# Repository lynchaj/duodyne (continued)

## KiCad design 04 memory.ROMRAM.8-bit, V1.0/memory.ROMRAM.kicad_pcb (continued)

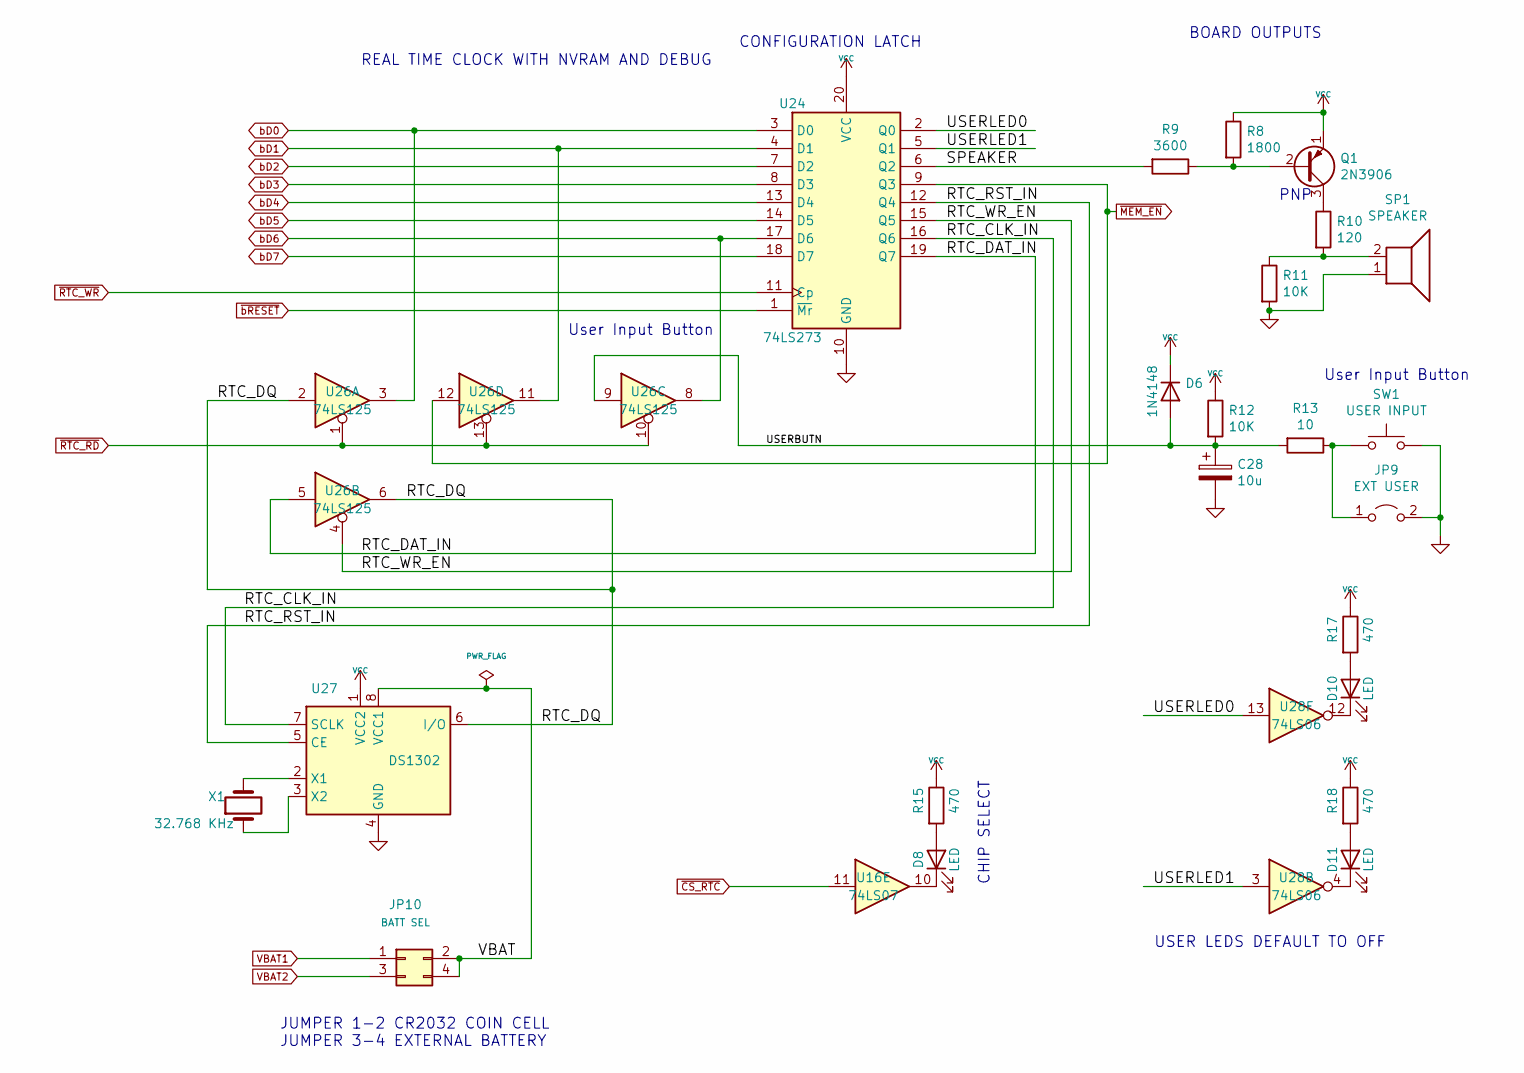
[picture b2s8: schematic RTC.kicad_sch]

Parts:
C28: 10u; CP_Radial_D5.0mm_P2.50mm
D6: 1N4148; D_DO-35_SOD27_P7.62mm_Horizontal
D8, D10, D11: LED; LED_D3.0mm_Horizontal_O3.81mm_Z2.0mm
JP9: EXT USER; PinHeader_1x02_P2.54mm_Horizontal
JP10: BATT SEL; PinHeader_2x02_P2.54mm_Vertical
Q1: 2N3906; TO-92_Inline
R8: 1800; R_Axial_DIN0207_L6.3mm_D2.5mm_P7.62mm_Horizontal
R9: 3600; R_Axial_DIN0207_L6.3mm_D2.5mm_P7.62mm_Horizontal
R10: 120; R_Axial_DIN0207_L6.3mm_D2.5mm_P7.62mm_Horizontal
R11, R12: 10K; R_Axial_DIN0207_L6.3mm_D2.5mm_P7.62mm_Horizontal
R13: 10; R_Axial_DIN0207_L6.3mm_D2.5mm_P7.62mm_Horizontal
R15, R17, R18: 470; R_Axial_DIN0207_L6.3mm_D2.5mm_P7.62mm_Horizontal
SP1: SPEAKER; MagneticBuzzer_StarMicronics_HMB-06_HMB-12
SW1: USER INPUT; SW_Tactile_SPST_Angled_PTS645Vx58-2LFS
U16: 74LS07; DIP-14_W7.62mm
U24: 74LS273; DIP-20_W7.62mm
U26: 74LS125; DIP-14_W7.62mm
U27: DS1302; DIP-8_W7.62mm
U28: 74LS06; DIP-14_W7.62mm
X1: 32.768 KHz; Crystal_AT310_D3.0mm_L10.0mm_Horizontal

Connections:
/RTC/RTC_CLK_IN: U24.16 (Q6), U27.7 (SCLK)
/RTC/RTC_DAT_IN: U24.19 (Q7), U26.5
/RTC/RTC_DQ: U26.2, U26.6, U27.6 (I/O)
/RTC/RTC_RST_IN: U24.12 (Q4), U27.5 (CE)
/RTC/RTC_WR_EN: U24.15 (Q5), U26.4
/RTC/SPEAKER: R9.2, U24.6 (Q2)
/RTC/USERBUTN: C28.1, D6.2 (A), R12.2, R13.2, U26.9
/RTC/USERLED0: U24.2 (Q0), U28.13
/RTC/USERLED1: U24.5 (Q1), U28.3
/RTC/VBAT: JP10.2, JP10.4, U27.8 (VCC1)
GND: C28.2, JP9.2 (B), R11.2, SP1.1, SW1.2, U24.10 (GND), U27.4 (GND); also elsewhere on the board
unnamed: D8.1 (K), U16.10
unnamed: D8.2 (A), R15.2
unnamed: D10.1 (K), U28.12
unnamed: D10.2 (A), R17.2
unnamed: D11.1 (K), U28.4
unnamed: D11.2 (A), R18.2
unnamed: JP9.1 (A), R13.1, SW1.1
unnamed: Q1.2 (B), R8.2, R9.1
unnamed: Q1.3 (C), R10.1
unnamed: R10.2, R11.1, SP1.2
unnamed: U27.2 (X1), X1.2
unnamed: U27.3 (X2), X1.1
VBAT1: JP10.1; also elsewhere on the board
VBAT2: JP10.3; also elsewhere on the board
VCC: D6.1 (K), Q1.1 (E), R8.1, R12.1, R15.1, R17.1, R18.1, U24.20 (VCC), U27.1 (VCC2); also elsewhere on the board
bD0: U24.3 (D0), U26.3; also elsewhere on the board
bD1: U24.4 (D1), U26.11; also elsewhere on the board
bD2: U24.7 (D2); also elsewhere on the board
bD3: U24.8 (D3); also elsewhere on the board
bD4: U24.13 (D4); also elsewhere on the board
bD5: U24.14 (D5); also elsewhere on the board
bD6: U24.17 (D6), U26.8; also elsewhere on the board
bD7: U24.18 (D7); also elsewhere on the board
~CS_RTC: U16.11; also elsewhere on the board
~MEM_EN: U24.9 (Q3), U26.12; also elsewhere on the board
~RTC_RD: U26.1, U26.10, U26.13; also elsewhere on the board
~RTC_WR: U24.11 (Cp); also elsewhere on the board
~bRESET: U24.1 (~Mr); also elsewhere on the board

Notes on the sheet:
PNP
User Input Button
BOARD OUTPUTS
CONFIGURATION LATCH
JUMPER 1-2 CR2032 COIN CELL JUMPER 3-4 EXTERNAL BATTERY
CHIP SELECT
USER LEDS DEFAULT TO OFF
REAL TIME CLOCK WITH NVRAM AND DEBUG

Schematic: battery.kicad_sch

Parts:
BT1: Battery; BatteryHolder_Keystone_103_1x20mm
JP1, JP4, JP5, JP6, JP8, JP11, JP12, JP13: BYPASS; PinHeader_1x02_P2.54mm_Vertical
JP2: BATT SEL; PinHeader_2x02_P2.54mm_Vertical
K1: VCC TOL 0; PinHeader_1x03_P2.54mm_Vertical
K2: VCC TOL 2; PinHeader_1x03_P2.54mm_Vertical
K3: VCC TOL 3; PinHeader_1x03_P2.54mm_Vertical
K5: VCC TOL 1; PinHeader_1x03_P2.54mm_Vertical
U5, U13, U18, U19: DS1210; DIP-8_W7.62mm

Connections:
/battery/V2032: BT1.1 (+), JP2.1
GND: BT1.2 (-), JP2.3, K1.3, K2.3, K3.3, K5.3, U5.4 (GND), U13.4 (GND), U18.4 (GND), U19.4 (GND); also elsewhere on the board
unnamed: K1.2, U5.3 (TOL)
unnamed: K2.2, U18.3 (TOL)
unnamed: K3.2, U19.3 (TOL)
unnamed: K5.2, U13.3 (TOL)
VBAT1: JP2.2, U5.2 (VBAT1), U13.2 (VBAT1), U18.2 (VBAT1), U19.2 (VBAT1); also elsewhere on the board
VBAT2: JP2.4, U5.7 (VBAT2), U13.7 (VBAT2), U18.7 (VBAT2), U19.7 (VBAT2); also elsewhere on the board
VCC: JP1.1 (A), JP5.1 (A), JP8.1 (A), JP12.1 (A), U5.8 (VCCI), U13.8 (VCCI), U18.8 (VCCI), U19.8 (VCCI); also elsewhere on the board
VCC_SRAM0: JP1.2 (B), K1.1, U5.1 (VCCO); also elsewhere on the board
VCC_SRAM1: JP5.2 (B), K5.1, U13.1 (VCCO); also elsewhere on the board
VCC_SRAM2: JP8.2 (B), K2.1, U18.1 (VCCO); also elsewhere on the board
VCC_SRAM3: JP12.2 (B), K3.1, U19.1 (VCCO); also elsewhere on the board
~CEO0: JP4.2 (B), U5.6 (~CEO); also elsewhere on the board
~CEO1: JP6.2 (B), U13.6 (~CEO); also elsewhere on the board
~CEO2: JP11.2 (B), U18.6 (~CEO); also elsewhere on the board
~CEO3: JP13.2 (B), U19.6 (~CEO); also elsewhere on the board
~CS_RAM0: JP4.1 (A), U5.5 (~CE); also elsewhere on the board
~CS_RAM1: JP6.1 (A), U13.5 (~CE); also elsewhere on the board
~CS_RAM2: JP11.1 (A), U18.5 (~CE); also elsewhere on the board
~CS_RAM3: JP13.1 (A), U19.5 (~CE); also elsewhere on the board

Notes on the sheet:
NOTE: K1 VCC TOLERANCE 1-2 CLOSED 10% 2-3 CLOSED 5%
JP1 AND JP3 U2 DS1210 INSTALLED CLOSE BOTH TO BYPASS DEFAULT BOTH OPEN
NOTE: K5 VCC TOLERANCE 1-2 CLOSED 10% 2-3 CLOSED 5%
JUMPER 1-2 CR2032 COIN CELL JUMPER 3-4 EXTERNAL BATTERY
JP4 AND JP5 U11 DS1210 INSTALLED CLOSE BOTH TO BYPASS DEFAULT BOTH OPEN

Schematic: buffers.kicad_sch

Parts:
U6, U7, U8, U17: 74LS244; DIP-20_W7.62mm
U14: 74LS245; DIP-20_W7.62mm

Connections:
A0: U6.2 (I0a); also elsewhere on the board
A1: U6.4 (I1a); also elsewhere on the board
A2: U6.6 (I2a); also elsewhere on the board
A3: U6.8 (I3a); also elsewhere on the board
A4: U6.11 (I0b); also elsewhere on the board
A5: U6.13 (I1b); also elsewhere on the board
A6: U6.15 (I2b); also elsewhere on the board
A7: U6.17 (I3b); also elsewhere on the board
A8: U7.2 (I0a); also elsewhere on the board
A9: U7.4 (I1a); also elsewhere on the board
A10: U7.6 (I2a); also elsewhere on the board
A11: U7.8 (I3a); also elsewhere on the board
A12: U7.11 (I0b); also elsewhere on the board
A13: U7.13 (I1b); also elsewhere on the board
A14: U7.15 (I2b); also elsewhere on the board
A15: U7.17 (I3b); also elsewhere on the board
A16: U8.2 (I0a); also elsewhere on the board
A17: U8.4 (I1a); also elsewhere on the board
A18: U8.6 (I2a); also elsewhere on the board
A19: U8.8 (I3a); also elsewhere on the board
A20: U8.11 (I0b); also elsewhere on the board
A21: U8.13 (I1b); also elsewhere on the board
D0: U14.2 (A0); also elsewhere on the board
D1: U14.3 (A1); also elsewhere on the board
D2: U14.4 (A2); also elsewhere on the board
D3: U14.5 (A3); also elsewhere on the board
D4: U14.6 (A4); also elsewhere on the board
D5: U14.7 (A5); also elsewhere on the board
D6: U14.8 (A6); also elsewhere on the board
D7: U14.9 (A7); also elsewhere on the board
GND: U6.10 (GND), U7.10 (GND), U8.10 (GND), U14.10 (GND), U17.10 (GND); also elsewhere on the board
unnamed 146: U17.2 (I0a); also elsewhere on the board
VCC: U6.20 (VCC), U7.20 (VCC), U8.20 (VCC), U14.20 (VCC), U17.20 (VCC); also elsewhere on the board
ZERO: U6.1 (OEa), U6.19 (OEb), U7.1 (OEa), U7.19 (OEb), U8.1 (OEa), U8.19 (OEb), U17.1 (OEa), U17.19 (OEb); also elsewhere on the board
bA0: U6.18 (O0a); also elsewhere on the board
bA1: U6.16 (O1a); also elsewhere on the board
bA2: U6.14 (O2a); also elsewhere on the board
bA3: U6.12 (O3a); also elsewhere on the board
bA4: U6.9 (O0b); also elsewhere on the board
bA5: U6.7 (O1b); also elsewhere on the board
bA6: U6.5 (O2b); also elsewhere on the board
bA7: U6.3 (O3b); also elsewhere on the board
bA8: U7.18 (O0a); also elsewhere on the board
bA9: U7.16 (O1a); also elsewhere on the board
bA10: U7.14 (O2a); also elsewhere on the board
bA11: U7.12 (O3a); also elsewhere on the board
bA12: U7.9 (O0b); also elsewhere on the board
bA13: U7.7 (O1b); also elsewhere on the board
bA14: U7.5 (O2b); also elsewhere on the board
bA15: U7.3 (O3b); also elsewhere on the board
bA16: U8.18 (O0a); also elsewhere on the board
bA17: U8.16 (O1a); also elsewhere on the board
bA18: U8.14 (O2a); also elsewhere on the board
bA19: U8.12 (O3a); also elsewhere on the board
bA20: U8.9 (O0b); also elsewhere on the board
bA21: U8.7 (O1b); also elsewhere on the board
bD0: U14.18 (B0); also elsewhere on the board
bD1: U14.17 (B1); also elsewhere on the board
bD2: U14.16 (B2); also elsewhere on the board
bD3: U14.15 (B3); also elsewhere on the board
bD4: U14.14 (B4); also elsewhere on the board
bD5: U14.13 (B5); also elsewhere on the board
bD6: U14.12 (B6); also elsewhere on the board
bD7: U14.11 (B7); also elsewhere on the board
~BUS_EN: U14.19 (CE); also elsewhere on the board
~IORQ: U17.11 (I0b); also elsewhere on the board
~M1: U17.8 (I3a); also elsewhere on the board
~MREQ: U17.13 (I1b); also elsewhere on the board
~RD: U14.1 (A->B), U17.17 (I3b); also elsewhere on the board
~WR: U17.15 (I2b); also elsewhere on the board
~bIORQ: U17.9 (O0b); also elsewhere on the board
~bM1: U17.12 (O3a); also elsewhere on the board
~bMREQ: U17.7 (O1b); also elsewhere on the board
~bRD: U17.3 (O3b); also elsewhere on the board
~bRESET: U17.18 (O0a); also elsewhere on the board
~bWR: U17.5 (O2b); also elsewhere on the board

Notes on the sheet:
Z80 BUS INTERFACE
Note: Buffers and Transceivers respond to both IO and MEM cycles

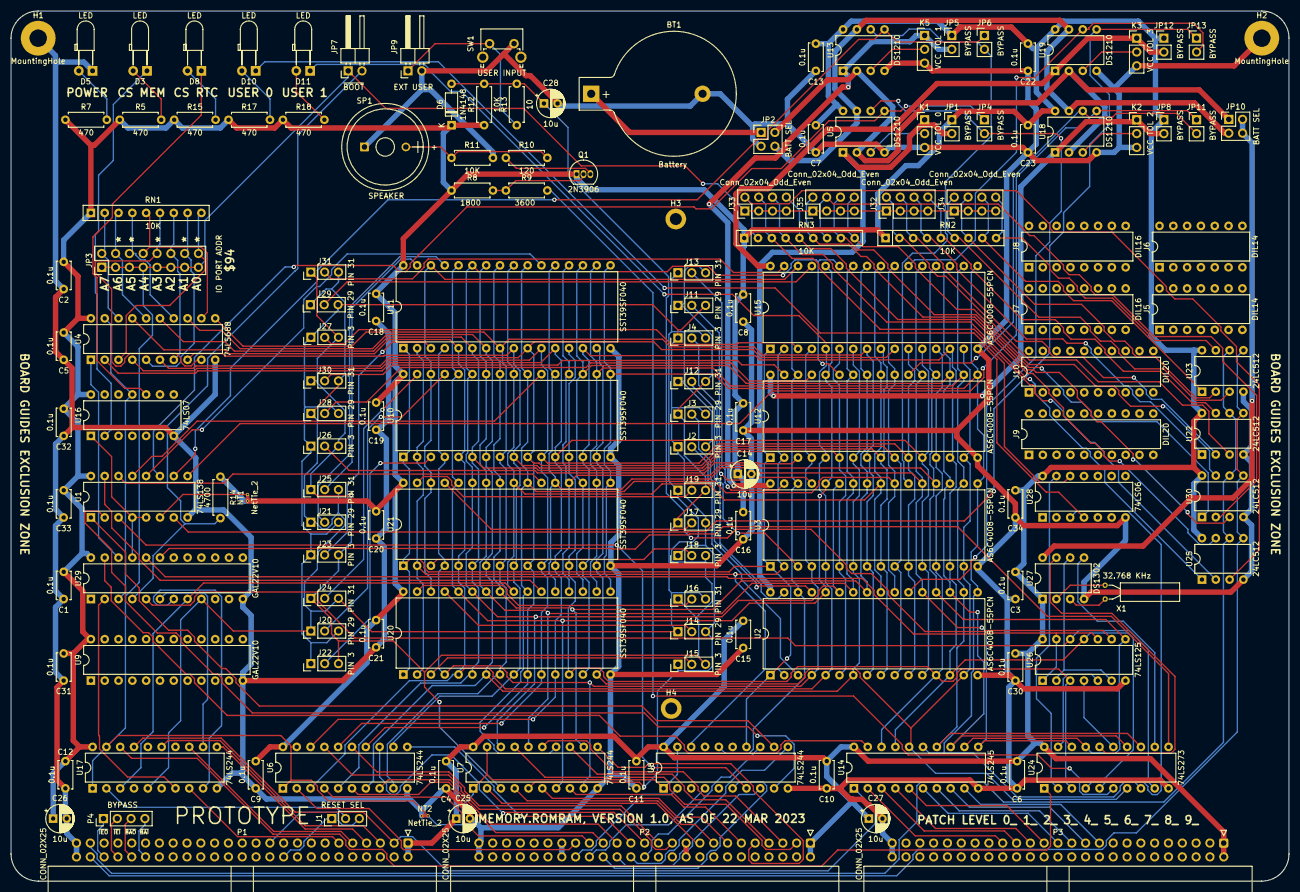
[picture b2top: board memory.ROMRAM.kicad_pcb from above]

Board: 2 copper layers, 235.0 x 160.0 mm, 150 parts (0 on the bottom side), 190 nets.

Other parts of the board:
J1: RESET SEL; PinHeader_1x03_P2.54mm_Vertical
J32, J33, J34, J35: Conn_02x04_Odd_Even; PinHeader_2x04_P2.54mm_Vertical
NT1, NT2: NetTie_2; NetTie-2_THT_Pad0.3mm
RN2, RN3: 10K; R_Array_SIP9
U22, U23, U25, U30: 24LC512; DIP-8_W7.62mm

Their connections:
GND: NT2.1, U22.4 (GND), U23.4 (GND), U25.4 (GND), U30.4 (GND); also elsewhere on the board
I2C_SCL: U22.6 (SCL), U23.6 (SCL), U25.6 (SCL), U30.6 (SCL); also elsewhere on the board
I2C_SDA: U22.5 (SDA), U23.5 (SDA), U25.5 (SDA), U30.5 (SDA); also elsewhere on the board
unnamed 146: J1.2; also elsewhere on the board
unnamed: J32.2, RN2.2 (R1), U22.3 (A2)
unnamed: J32.4, RN2.3 (R2), U22.2 (A1)
unnamed: J32.6, RN2.4 (R3), U22.1 (A0)
unnamed: J32.8, RN2.5 (R4), U22.7 (WP)
unnamed: J33.2, RN3.2 (R1), U25.3 (A2)
unnamed: J33.4, RN3.3 (R2), U25.2 (A1)
unnamed: J33.6, RN3.4 (R3), U25.1 (A0)
unnamed: J33.8, RN3.5 (R4), U25.7 (WP)
unnamed: J34.2, RN2.6 (R5), U23.3 (A2)
unnamed: J34.4, RN2.7 (R6), U23.2 (A1)
unnamed: J34.6, RN2.8 (R7), U23.1 (A0)
unnamed: J34.8, RN2.9 (R8), U23.7 (WP)
unnamed: J35.2, RN3.6 (R5), U30.3 (A2)
unnamed: J35.4, RN3.7 (R6), U30.2 (A1)
unnamed: J35.6, RN3.8 (R7), U30.1 (A0)
unnamed: J35.8, RN3.9 (R8), U30.7 (WP)
ONE: NT1.2; also elsewhere on the board
VCC: NT1.1, RN2.1 (common), RN3.1 (common), U22.8 (VCC), U23.8 (VCC), U25.8 (VCC), U30.8 (VCC); also elsewhere on the board
ZERO: J32.1, J32.3, J32.5, J32.7, J33.1, J33.3, J33.5, J33.7, J34.1, J34.3, J34.5, J34.7, J35.1, J35.3, J35.5, J35.7, NT2.2; also elsewhere on the board
~RES_IN: J1.1; also elsewhere on the board
~RES_OUT: J1.3; also elsewhere on the board

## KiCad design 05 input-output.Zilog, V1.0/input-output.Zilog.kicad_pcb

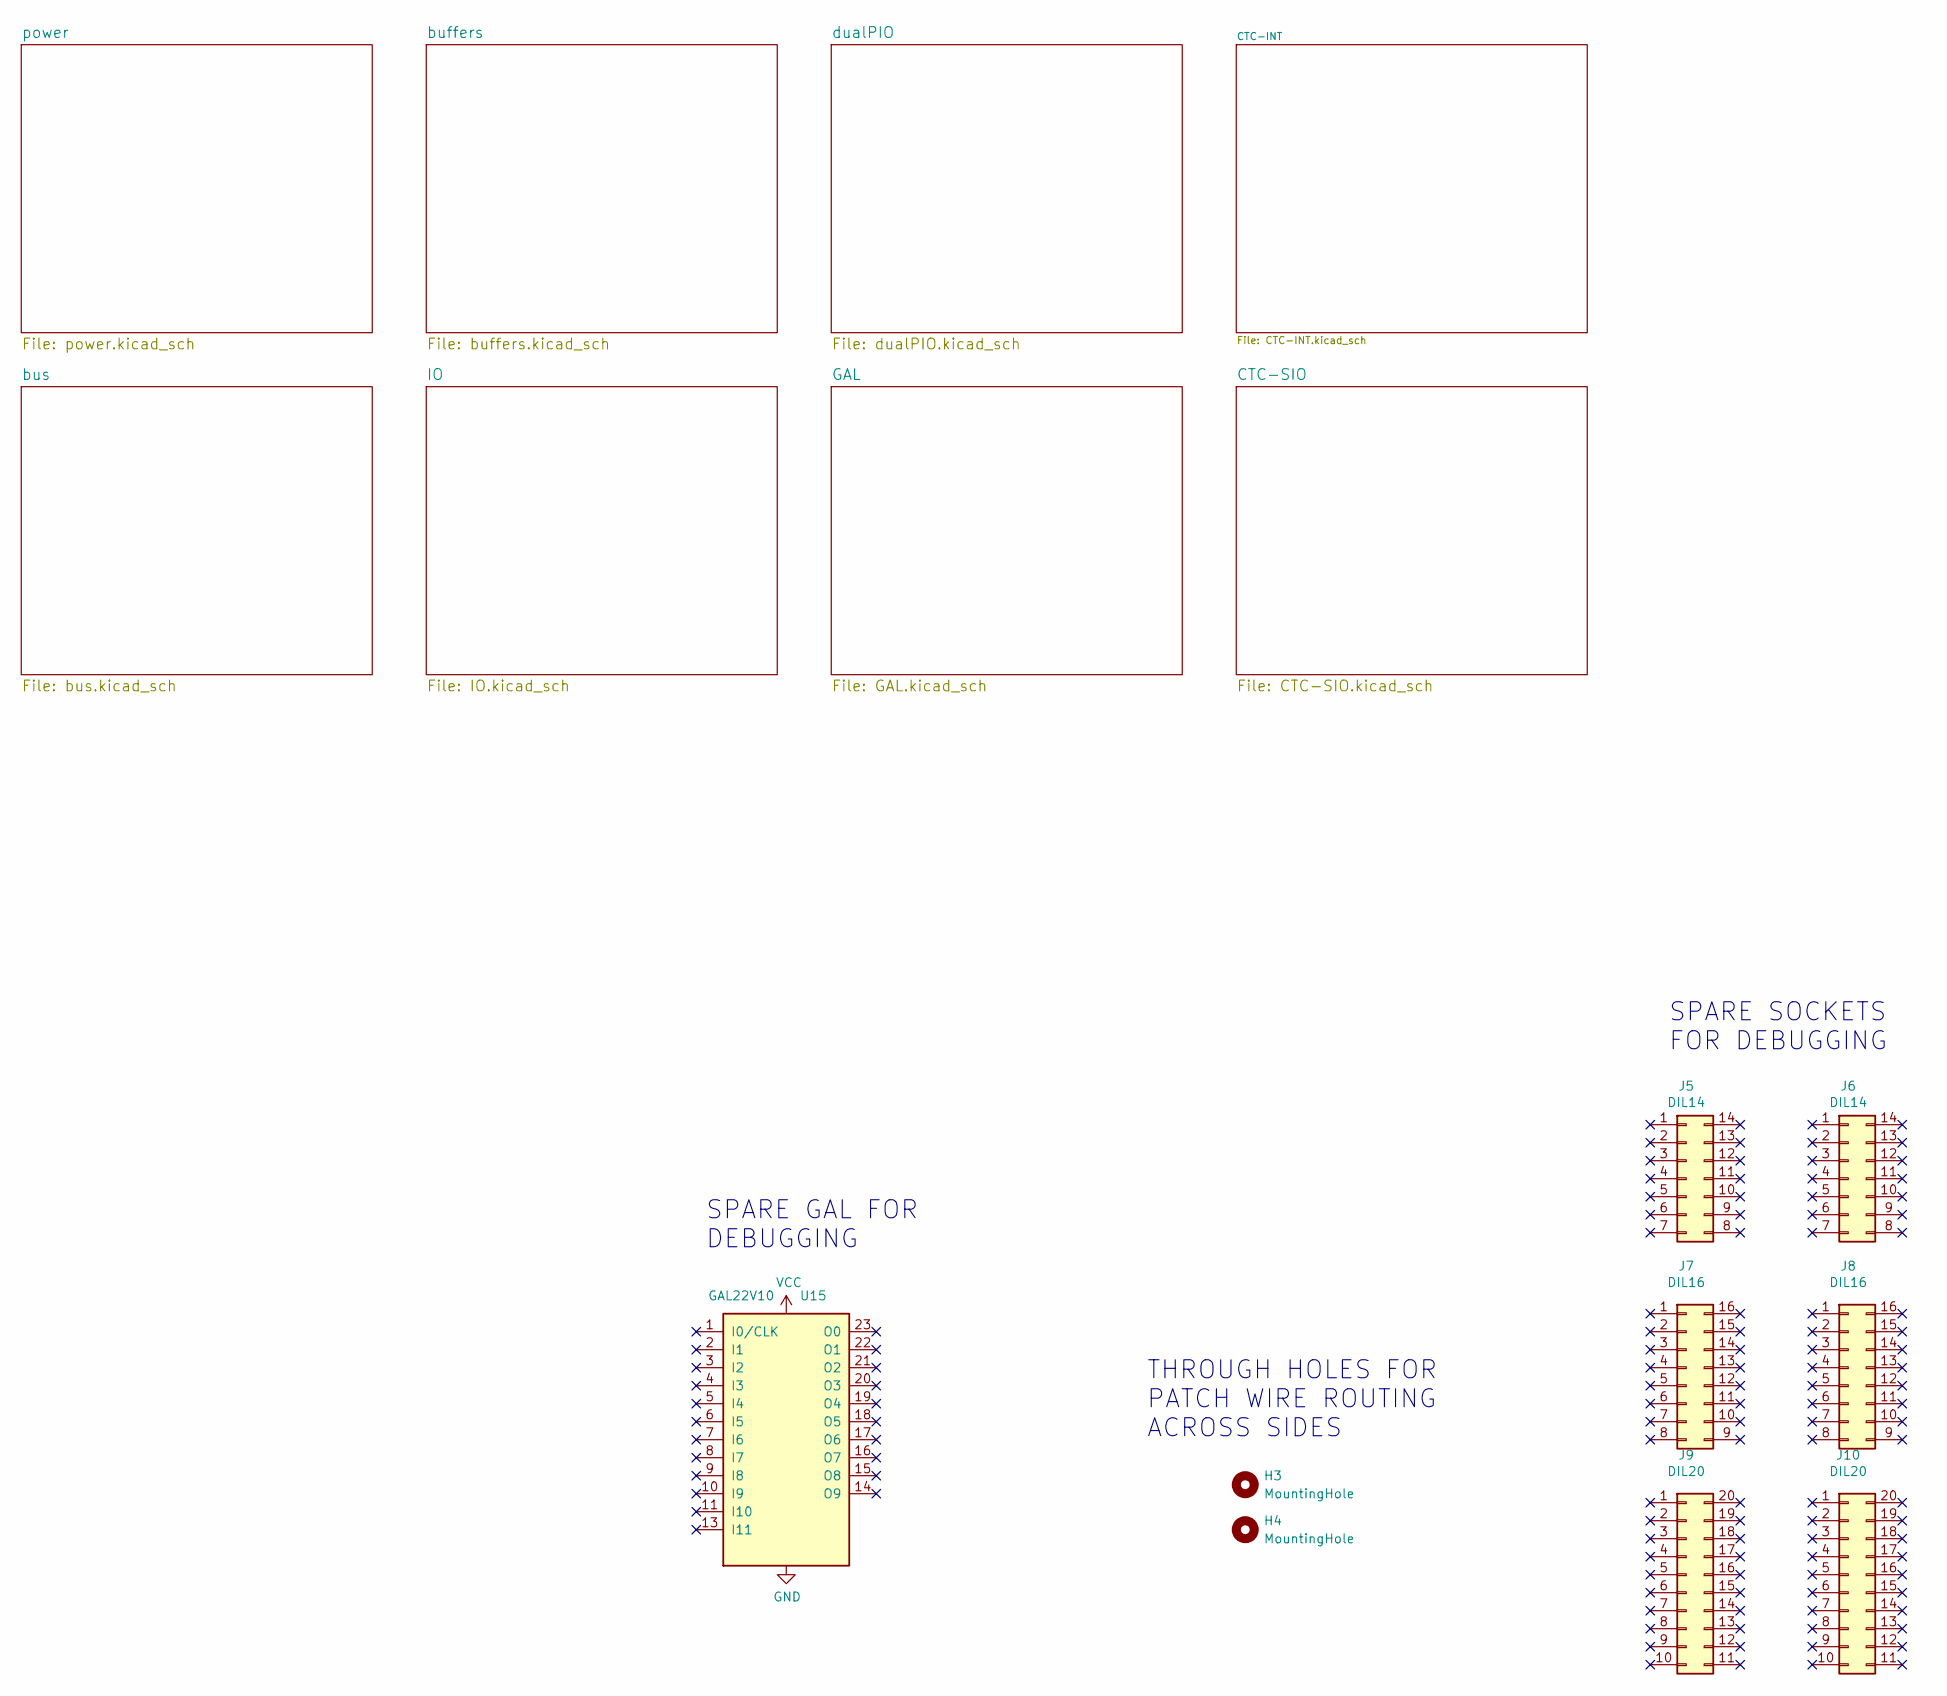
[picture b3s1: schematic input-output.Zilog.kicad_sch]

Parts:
H3, H4: MountingHole; MountingHole_2.2mm_M2_DIN965_Pad
J5, J6: DIL14; DIP-14_W7.62mm
J7, J8: DIL16; DIP-16_W7.62mm
J9, J10: DIL20; DIP-20_W7.62mm
U15: GAL22V10; DIP-24_W7.62mm

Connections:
GND: U15.12 (GND); also elsewhere on the board
VCC: U15.24 (VCC); also elsewhere on the board

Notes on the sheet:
THROUGH HOLES FOR PATCH WIRE ROUTING ACROSS SIDES
SPARE GAL FOR DEBUGGING
SPARE SOCKETS FOR DEBUGGING

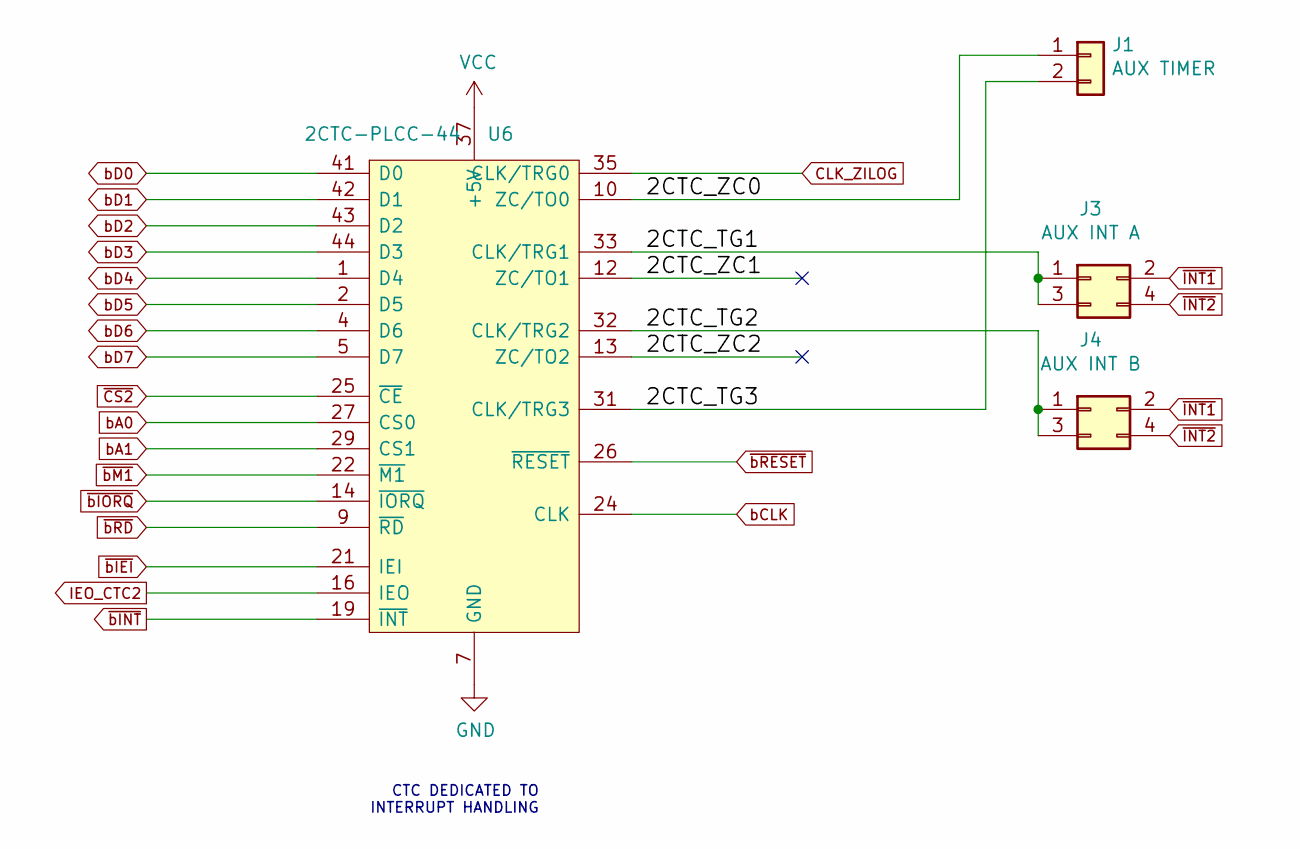
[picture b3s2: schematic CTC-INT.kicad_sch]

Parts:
J1: AUX TIMER; PinHeader_1x02_P2.54mm_Vertical
J3: AUX INT A; PinHeader_2x02_P2.54mm_Vertical
J4: AUX INT B; PinHeader_2x02_P2.54mm_Vertical
U6: 2CTC-PLCC-44; PLCC-44_16.6x16.6mm_P1.27mm; Manufacturer_Part_Number Z84C3010PEG; Mouser Part Number 692-Z84C3010PEG

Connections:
/CTC-INT/2CTC_TG1: J3.1, J3.3, U6.33 (CLK/TRG1)
/CTC-INT/2CTC_TG2: J4.1, J4.3, U6.32 (CLK/TRG2)
/CTC-INT/2CTC_TG3: J1.2, U6.31 (CLK/TRG3)
/CTC-INT/2CTC_ZC0: J1.1, U6.10 (ZC/TO0)
/CTC-INT/2CTC_ZC1: U6.12 (ZC/TO1)
/CTC-INT/2CTC_ZC2: U6.13 (ZC/TO2)
CLK_ZILOG: U6.35 (CLK/TRG0); also elsewhere on the board
GND: U6.7 (GND); also elsewhere on the board
IEO_CTC2: U6.16 (IEO); also elsewhere on the board
VCC: U6.37 (+5V); also elsewhere on the board
bA0: U6.27 (CS0); also elsewhere on the board
bA1: U6.29 (CS1); also elsewhere on the board
bCLK: U6.24 (CLK); also elsewhere on the board
bD0: U6.41 (D0); also elsewhere on the board
bD1: U6.42 (D1); also elsewhere on the board
bD2: U6.43 (D2); also elsewhere on the board
bD3: U6.44 (D3); also elsewhere on the board
bD4: U6.1 (D4); also elsewhere on the board
bD5: U6.2 (D5); also elsewhere on the board
bD6: U6.4 (D6); also elsewhere on the board
bD7: U6.5 (D7); also elsewhere on the board
~CS2: U6.25 (~CE); also elsewhere on the board
~INT1: J3.2, J4.2; also elsewhere on the board
~INT2: J3.4, J4.4; also elsewhere on the board
~bIEI: U6.21 (IEI); also elsewhere on the board
~bINT: U6.19 (~INT); also elsewhere on the board
~bIORQ: U6.14 (~IORQ); also elsewhere on the board
~bM1: U6.22 (~M1); also elsewhere on the board
~bRD: U6.9 (~RD); also elsewhere on the board
~bRESET: U6.26 (~RESET); also elsewhere on the board

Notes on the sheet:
CTC DEDICATED TO INTERRUPT HANDLING

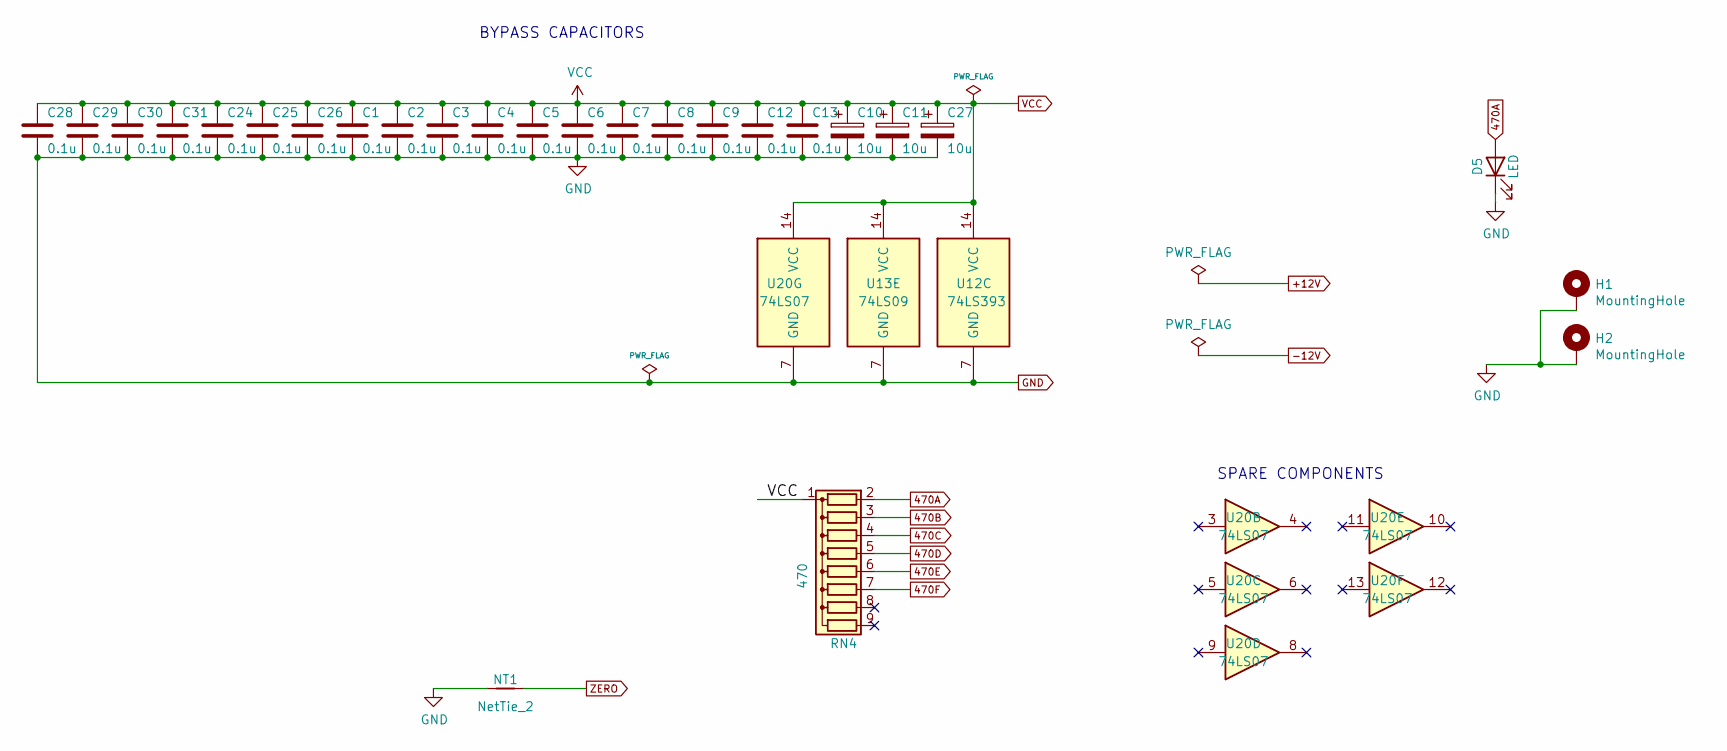
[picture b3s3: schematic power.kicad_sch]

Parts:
C1, C2, C3, C4, C5, C6, C7, C8, C9, C12, C13, C24, C25, C26, C28, C29, C30, C31: 0.1u; C_Disc_D5.0mm_W2.5mm_P5.00mm
C10, C11, C27: 10u; CP_Radial_D5.0mm_P2.50mm
D5: LED; LED_D3.0mm_Horizontal_O3.81mm_Z2.0mm
H1, H2: MountingHole; MountingHole_3.2mm_M3_Pad
NT1: NetTie_2; NetTie-2_THT_Pad0.3mm
RN4: 470; R_Array_SIP9
U12: 74LS393; DIP-14_W7.62mm
U13: 74LS09; DIP-14_W7.62mm
U20: 74LS07; DIP-14_W7.62mm

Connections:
470A: D5.2 (A), RN4.2 (R1)
470B: RN4.3 (R2); also elsewhere on the board
470C: RN4.4 (R3); also elsewhere on the board
470D: RN4.5 (R4); also elsewhere on the board
470E: RN4.6 (R5); also elsewhere on the board
470F: RN4.7 (R6); also elsewhere on the board
GND: C1.2, C2.2, C3.2, C4.2, C5.2, C6.2, C7.2, C8.2, C9.2, C10.2, C11.2, C12.2, C13.2, C24.2, C25.2, C26.2, C27.2, C28.2, C29.2, C30.2, C31.2, D5.1 (K), H1.1, H2.1, NT1.1, U12.7 (GND), U13.7 (GND), U20.7 (GND); also elsewhere on the board
VCC: C1.1, C2.1, C3.1, C4.1, C5.1, C6.1, C7.1, C8.1, C9.1, C10.1, C11.1, C12.1, C13.1, C24.1, C25.1, C26.1, C27.1, C28.1, C29.1, C30.1, C31.1, RN4.1 (common), U12.14 (VCC), U13.14 (VCC), U20.14 (VCC); also elsewhere on the board
ZERO: NT1.2; also elsewhere on the board

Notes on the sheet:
BYPASS CAPACITORS
SPARE COMPONENTS
